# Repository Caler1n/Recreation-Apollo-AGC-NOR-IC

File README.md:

# Recreation-Apollo-AGC-NOR-IC

Recreation Apollo AGC Block II Dual NOR IC

A Dual 3-Input NOR Gate in a DIP-10 Package. 

## Pictures

## Schematic
[Dual NOR - Schematic .pdf](Files/Dual-NOR-Schematics.pdf)

## Pinout
  
**From The Virtual AGC Project**
## Bill of Materials (BOM)
| **Component type** | **Reference** | **Description** | **Quantity** | **Sources** | Footprint |
| :----------------- | :------------ | :-------------- | :----------- | :----------------------------- | :----|
|PCB| |Dual NOR PCB| 1 | [Oshpark](https://oshpark.com/shared_projects/wMJdI9ql) | |
|Connector | J1|01x05 Pin Header | 2| Digikey [2057-PH1-05-UA-ND](https://www.digikey.com/en/products/detail/adam-tech/PH1-05-UA/9830343) | PinHeader 01x05 P2.54mm
|NPN BJT Transistor | Q1-Q6 | PBMT2369 | 6 | Digikey [1727-PMBT2369,235CT-ND](https://www.digikey.com/en/products/detail/nexperia-usa-inc/PMBT2369-235/1157634) | SOT-23|
| Resistor | R1, R5 | 680 Ohm | 2 | Digikey [13-RC0603JR-13680RLCT-ND](https://www.digikey.com/en/products/detail/yageo/RC0603JR-13680RL/14286446) | 0603 |
| Resistor | R2, R3, R4, R6, R7, R8 | 470 Ohm | 6 | Digikey [13-RC0603FR-13470RLCT-ND](https://www.digikey.com/en/products/detail/yageo/RC0603FR-13470RL/13694077) | 0603 |

## Power Supply
The recreation IC requies a regulated 4V power supply.

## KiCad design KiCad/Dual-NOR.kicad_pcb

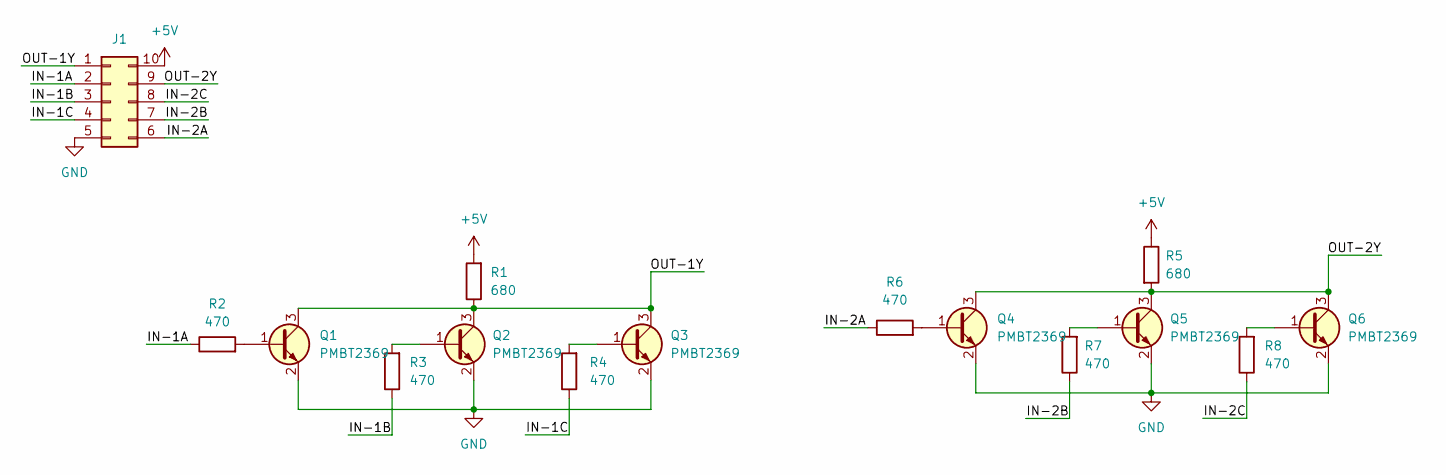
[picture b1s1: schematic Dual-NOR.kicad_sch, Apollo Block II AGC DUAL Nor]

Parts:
J1: DIP-10_W7.62mm_Socket
Q1, Q2, Q3, Q4, Q5, Q6: PMBT2369; SOT-23
R1, R5: 680; R_0603_1608Metric
R2, R3, R4, R6, R7, R8: 470; R_0603_1608Metric

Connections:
+5V: J1.10, R1.2, R5.1
/IN-1A: J1.2, R2.1
/IN-1B: J1.3, R3.1
/IN-1C: J1.4, R4.1
/IN-2A: J1.6, R6.1
/IN-2B: J1.7, R7.1
/IN-2C: J1.8, R8.1
/OUT-1Y: J1.1, Q1.3 (C), Q2.3 (C), Q3.3 (C), R1.1
/OUT-2Y: J1.9, Q4.3 (C), Q5.3 (C), Q6.3 (C), R5.2
GND: J1.5, Q1.2 (E), Q2.2 (E), Q3.2 (E), Q4.2 (E), Q5.2 (E), Q6.2 (E)
unnamed: Q1.1 (B), R2.2
unnamed: Q2.1 (B), R3.2
unnamed: Q3.1 (B), R4.2
unnamed: Q4.1 (B), R6.2
unnamed: Q5.1 (B), R7.2
unnamed: Q6.1 (B), R8.2

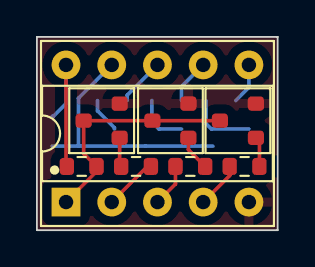
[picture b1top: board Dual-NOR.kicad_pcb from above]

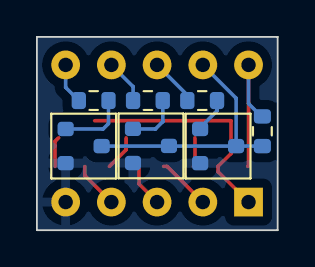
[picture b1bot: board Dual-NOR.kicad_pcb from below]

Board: 2 copper layers, 13.4 x 10.7 mm, 15 parts (7 on the bottom side), 16 nets.

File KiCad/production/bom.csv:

Designator,Footprint,Quantity,Value,LCSC Part #
J1,DIP-10_W7.62mm_Socket,1,~,
"Q1, Q2, Q3, Q4, Q5, Q6",SOT-23,6,PMBT2369,
"R1, R5",0603,2,680,
"R2, R3, R4, R6, R7, R8",0603,6,470,

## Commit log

2025-10-19 Init Commit
2025-10-19 Changed File Structure
2025-10-19 Added Schematic and Updated README
2025-10-19 Fixed Images in Readme
2025-10-19 Actually Fixed Pinout Image
